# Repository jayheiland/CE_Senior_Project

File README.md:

# Our Project: An Analog Synthesizer with a Digital Interface

## Project Overview
The goal of this senior project was to take
the best parts of both digital and analog synths and
combine them into a working, scalable prototype for an
analog synth with digital control. The core components of
this project consist of a software application, synthesizer
modules, and the software and hardware interfaces
between them. On Demo Day we were able to show off
the most important and core parts of our project.

## Project Structure
 - "app src" contains the source files for the supporting desktop app.
 - "docs" contains our final report. Context for this project and all citations can be found within the final report.
 - "embedded src" contains all embedded project files for our *STM32F072 Discovery* microcontroller.
 - "schematics" contains the design files for our printed circuit board and acrylic panels, plus a supporting .als (Ableton Live Session) file for processing musical keyboard input into MIDI output.

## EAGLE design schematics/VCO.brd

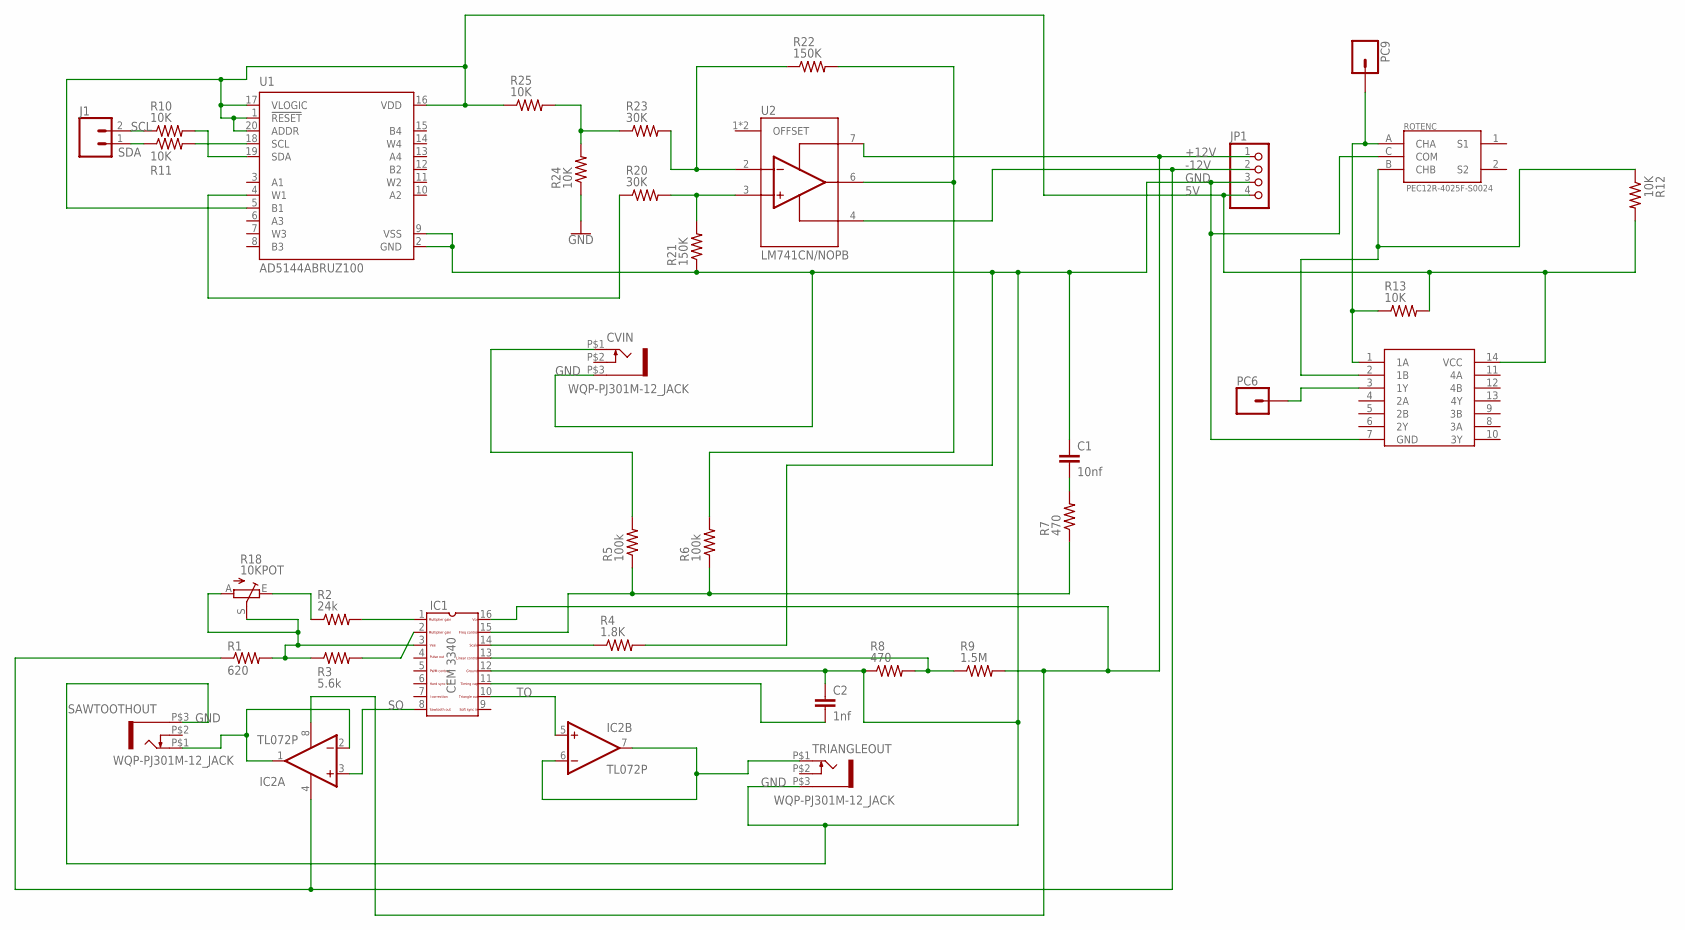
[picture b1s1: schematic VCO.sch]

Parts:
C1: 10nf; C2.5-3
C2: 1nf; C2.5-3
CVIN: WQP-PJ301M-12_JACK
IC1: CEM3340; DIL16
IC2: TL072P; DIL08
J1: CONN_02; 1X02
JP1: PINHD-1X4; 1X04
PC6, PC9: CONN_01; 1X01
R1: 620; 0207/10
R2: 24k; 0207/10
R3: 5.6k; 0207/10
R4: 1.8K; 0207/10
R5, R6: 100k; 0207/10
R7, R8: 470; 0207/10
R9: 1.5M; 0207/10
R10, R11, R12, R13, R24, R25: 10K; 0207/10
R18: 10KPOT; B25P
R20, R23: 30K; 0207/10
R21, R22: 150K; 0207/10
ROTENC: PEC12R-4025F-S0024; ENC_PEC12R-4025F-S0024
SAWTOOTHOUT: WQP-PJ301M-12_JACK
TRIANGLEOUT: WQP-PJ301M-12_JACK
U1: AD5144ABRUZ100; SOP65P640X120-20N
U2: LM741CN/NOPB; DIP794W45P254L1016H508Q8
XOR: SN54HC86; DIP762W51P254L1994H508Q14

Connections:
5V: JP1.4, R12.2, R13.2, R25.1, U1.1 (!RESET), U1.5 (B1), U1.16 (VDD), U1.17 (VLOGIC), U1.20 (ADDR), XOR.14 (VCC)
+12V: IC1.16, IC2.8 (V+), JP1.1, R9.2, U2.7 (V+)
-12V: IC2.4 (V-), JP1.2, R1.1, U2.4 (V-)
GND: C1.1, C2.1, CVIN.P$3 (1), IC1.12, JP1.3, R4.2, R8.1, R21.1, R24.1, ROTENC.C (COM), SAWTOOTHOUT.P$3 (1), TRIANGLEOUT.P$3 (1), U1.2 (GND), U1.9 (VSS), XOR.7 (GND)
unnamed: IC1.1, R2.2
unnamed: IC1.2, R3.2
unnamed: IC1.3, R1.2, R3.1, R18.A, R18.S
unnamed: PC9.1, R13.1, ROTENC.A (CHA), XOR.1 (1A)
unnamed: R12.1, ROTENC.B (CHB), XOR.2 (1B)
unnamed: IC1.14, R4.1
unnamed: IC1.15, R5.1, R6.1, R7.1
unnamed: R6.2, R22.2, U2.6 (OUTPUT)
unnamed: CVIN.P$1 (2), R5.2
unnamed: C1.2, R7.2
unnamed: IC2.6 (-IN), IC2.7 (OUT), TRIANGLEOUT.P$1 (2)
unnamed: IC1.13, R8.2, R9.1
unnamed: C2.2, IC1.11
unnamed: IC2.1 (OUT), IC2.2 (-IN), SAWTOOTHOUT.P$1 (2)
unnamed: R2.1, R18.E
unnamed: R11.2, U1.18 (SCL)
unnamed: R20.2, R21.2, U2.3 (NON-INV_INPUT)
unnamed: R22.1, R23.2, U2.2 (INV_INPUT)
unnamed: R23.1, R24.2, R25.2
unnamed: R20.1, U1.4 (W1)
unnamed: R10.2, U1.19 (SDA)
unnamed: PC6.1, XOR.3 (1Y)
SCL: J1.2, R10.1
SDA: J1.1, R11.1
SO: IC1.8, IC2.3 (+IN)
TO: IC1.10, IC2.5 (+IN)

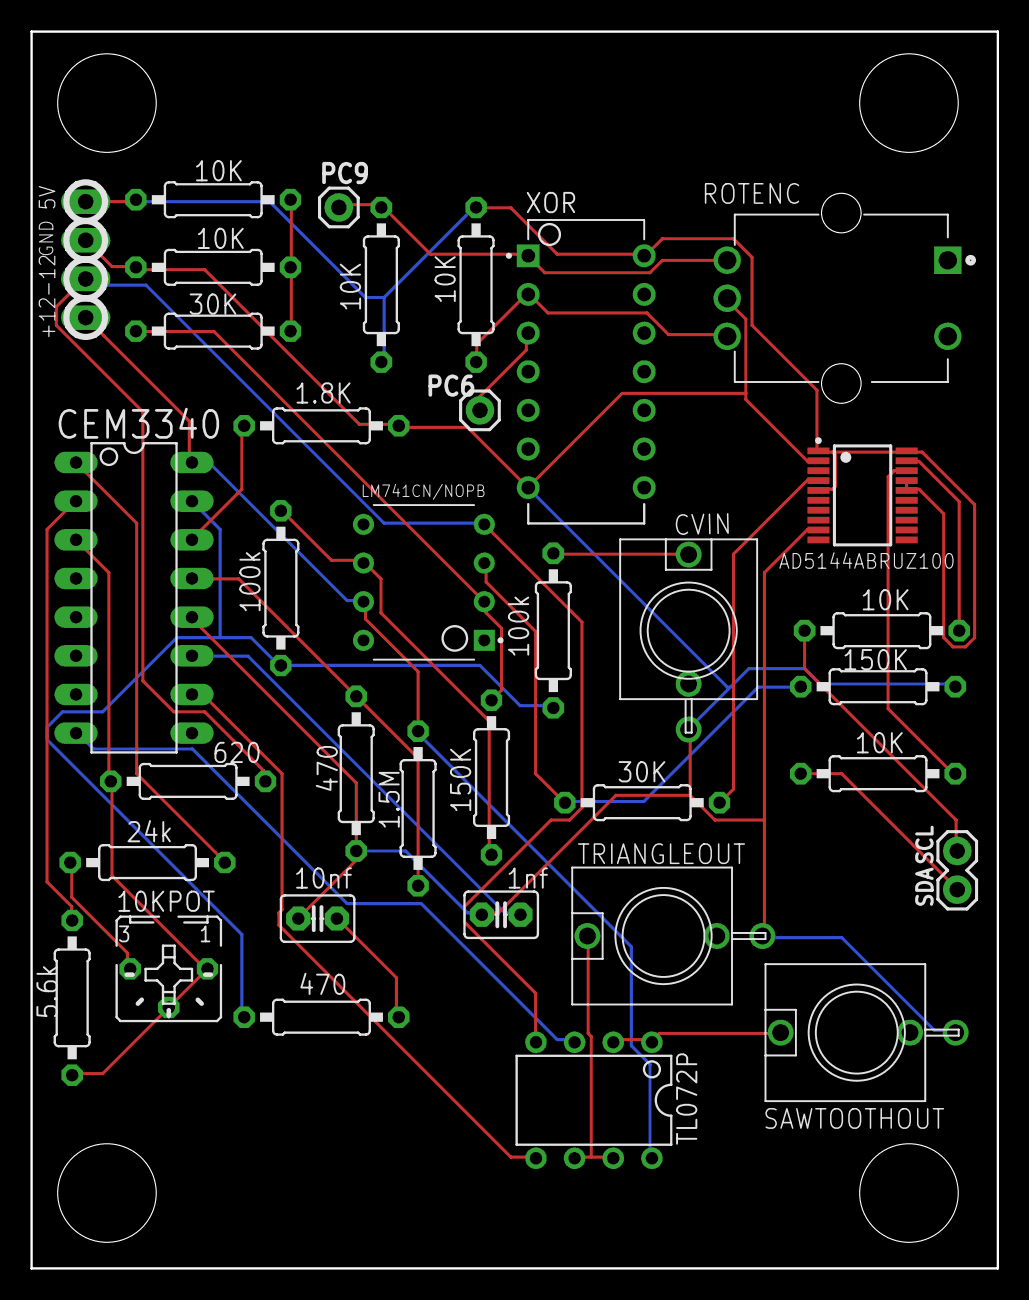
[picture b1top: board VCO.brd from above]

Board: 2 copper layers, 63.5 x 81.3 mm, 35 parts (0 on the bottom side), 30 nets.

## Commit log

2019-02-19 Set theme jekyll-theme-cayman
2019-02-19 Initial web page commit
2019-02-19 Link meeting logs on webpage
2019-05-01 Add prototype documentation
2019-08-28 Update meeting logs doc
2019-10-16 Initial commit for MySynth project
    Presets sidebar partially implemented, save/load functionality partially implemented
2019-10-17 Add modules GUI, improve save/load functionality
    Now opens save/load dialogs when clicking Save or Load buttons
2019-10-17 Improve save/load features
    Loaded preset values are displayed on the GUI modules after using the Load dialog, GUI module values can be saved to a .preset file with the Save dialog
2019-11-16 Add rough module reading code
2019-11-23 Add VCO writing and reading functionality
    Tested writing GUI text values to the VCO. Values are on a 0-255 scale, converted to hex when writing to VCO. Can read hex value from VCO.
2019-11-30 Add periodic calling of read_synth
2019-12-03 Parse and read values from digipot
    and write them to the corresponding GUI module
2019-12-05 add stm embedded code
2019-12-05 Add new resistor indexes for high pass/low pass filters
2019-12-06 Add switching/closing preset pips functionality
2019-12-06 Remove time parameter from restart_read_timer
    This fixes a weird problem with bad values being read/written to the STM
2019-12-06 Fix threading problem preventing writing from presets
2019-12-06 Add cancel calls for read_timer to prevent the creation of too many threads
2019-12-14 embedded C code for digipot & rotary encoder, USART
2020-01-23 State of desktop app at senior project presentation
2020-01-23 Reorganize project folders, add source files for final report and supporting components
2020-01-23 Add progress reports to docs/fall 2019 docs
2020-01-23 Remove embedded drivers, libs, extraneous files
2020-03-05 Add back necessary embedded source files

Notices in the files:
parts and their libraries:
SparkFun-Connectors: Licensing: Creative Commons ShareAlike 4.0 International - https://creativecommons.org/licenses/by-sa/4.0
